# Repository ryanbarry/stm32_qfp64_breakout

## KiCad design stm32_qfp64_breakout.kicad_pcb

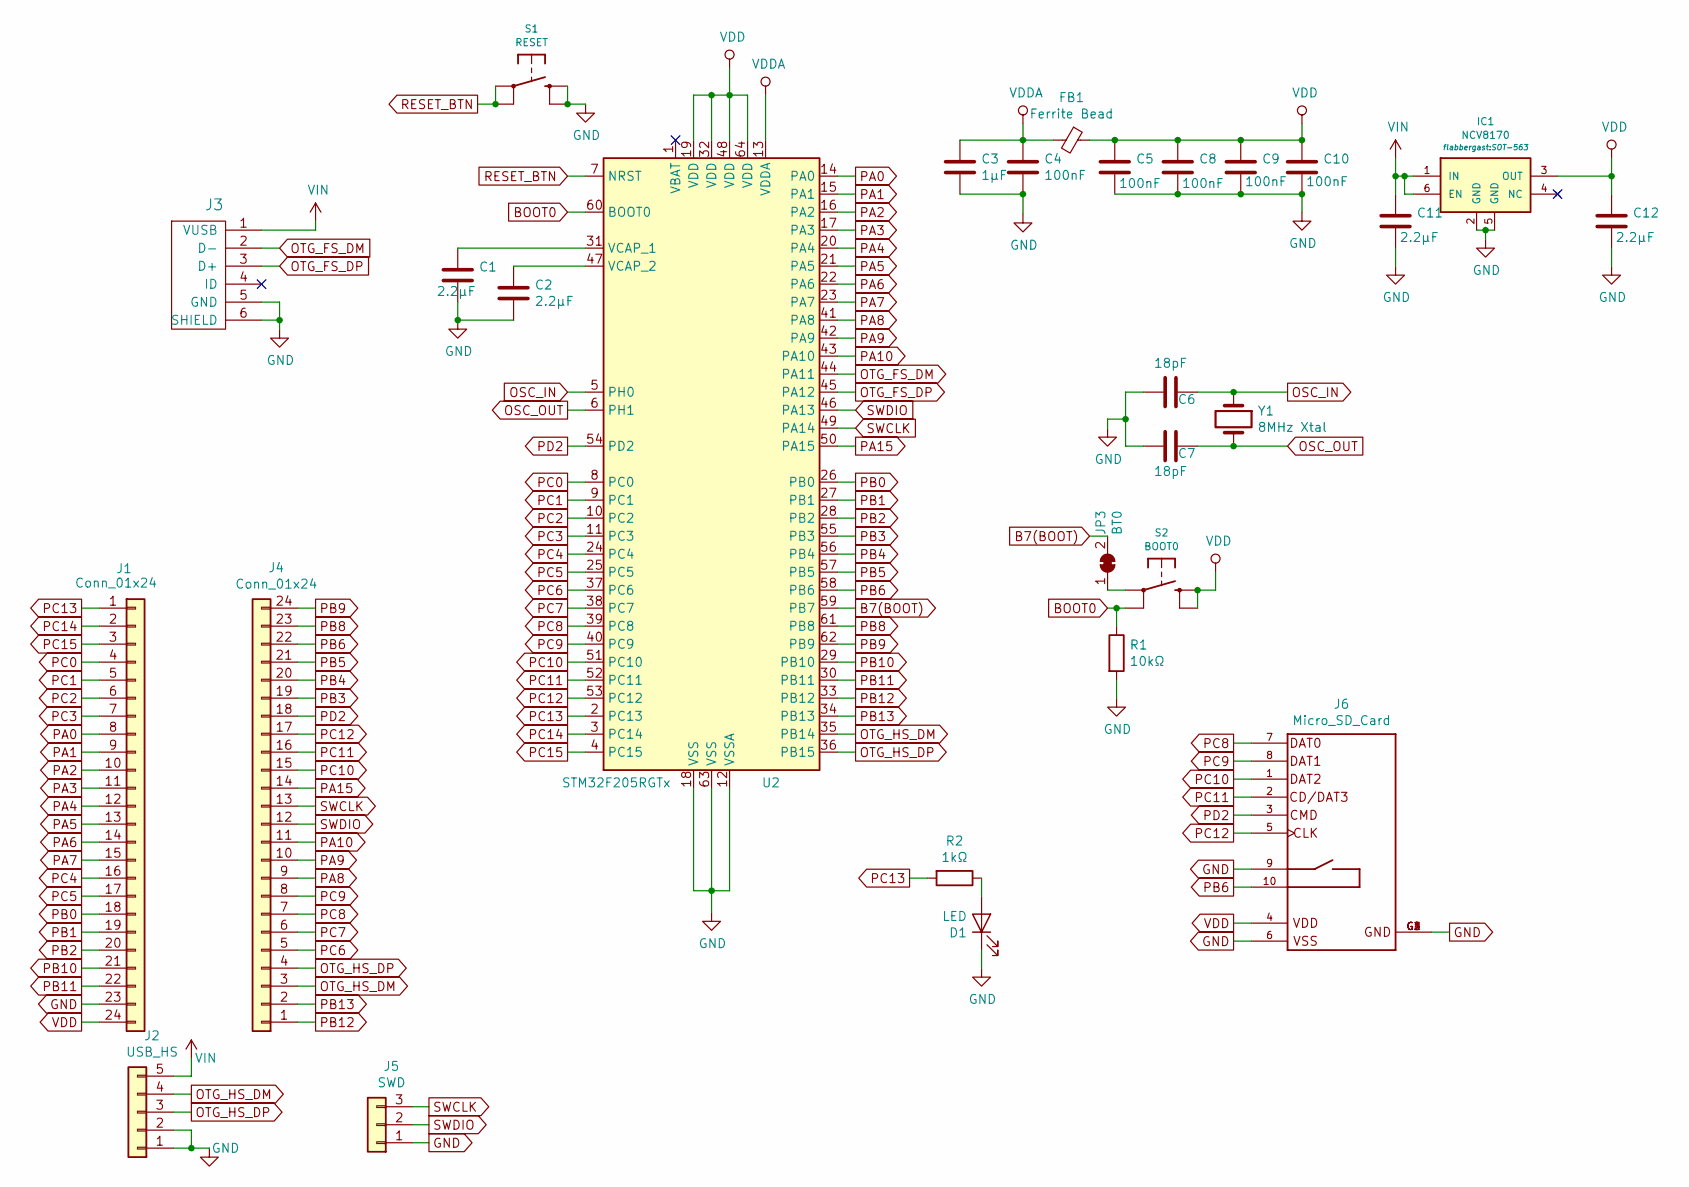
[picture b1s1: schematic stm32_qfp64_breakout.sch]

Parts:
C1, C2, C11, C12: 2.2µF; C_0603_1608Metric
C3: 1µF; C_0603_1608Metric
C4, C5, C8, C9, C10: 100nF; C_0603_1608Metric
C6, C7: 18pF; C_0603_1608Metric
D1: LED; LED-0603
FB1: Ferrite Bead; L_0603_1608Metric
IC1: NCV8170; SOT-563
J1, J4: Conn_01x24; M24_LOCK_NOSILK
J2: USB_HS; PinHeader_1x05_P2.54mm_Vertical
J3: USB_mini_micro_B; USB_microB_2TH_OSHPARK
J5: SWD; PinHeader_1x03_P2.54mm_Vertical
J6: Micro_SD_Card; MOLEX_104031-0811
JP3: BT0; SolderJumper-2_P1.3mm_Open_RoundedPad1.0x1.5mm
R1: 10kΩ; R_0603_1608Metric
R2: 1kΩ; 0603
S1: RESET; TACTILE-SWITCH-SMT-4x3
S2: BOOT0; TACTILE-SWITCH-SMT-4x3
U2: STM32F205RGTx; LQFP-64_10x10mm_P0.5mm
Y1: 8MHz Xtal; CRYSTAL-ABM3

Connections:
B7(BOOT): JP3.2 (B), U2.59 (PB7)
BOOT0: R1.1, S2.2, U2.60 (BOOT0)
GND: C1.1, C2.2, C3.2, C4.2, C5.2, C6.2, C7.2, C8.2, C9.2, C10.2, C11.2, C12.2, D1.1 (K), IC1.2 (GND), IC1.5 (GND), J1.23, J2.1, J2.2, J3.5 (GND), J3.6 (SHIELD), J5.1, J6.6 (VSS), J6.9 (CARD_DET1), J6.G1 (GND), J6.G2 (GND), J6.G3 (GND), J6.G4 (GND), R1.2, S1.3, S1.4, U2.12 (VSSA), U2.18 (VSS), U2.63 (VSS)
unnamed: C1.2, U2.31 (VCAP_1)
unnamed: C2.1, U2.47 (VCAP_2)
unnamed: D1.2 (A), R2.1
unnamed: JP3.1 (A), S2.1
OSC_IN: C6.1, U2.5 (PH0), Y1.1
OSC_OUT: C7.1, U2.6 (PH1), Y1.2
OTG_FS_DM: J3.2 (D-), U2.44 (PA11)
OTG_FS_DP: J3.3 (D+), U2.45 (PA12)
OTG_HS_DM: J2.4, J4.3, U2.35 (PB14)
OTG_HS_DP: J2.3, J4.4, U2.36 (PB15)
PA0: J1.8, U2.14 (PA0)
PA1: J1.9, U2.15 (PA1)
PA2: J1.10, U2.16 (PA2)
PA3: J1.11, U2.17 (PA3)
PA4: J1.12, U2.20 (PA4)
PA5: J1.13, U2.21 (PA5)
PA6: J1.14, U2.22 (PA6)
PA7: J1.15, U2.23 (PA7)
PA8: J4.9, U2.41 (PA8)
PA9: J4.10, U2.42 (PA9)
PA10: J4.11, U2.43 (PA10)
PA15: J4.14, U2.50 (PA15)
PB0: J1.18, U2.26 (PB0)
PB1: J1.19, U2.27 (PB1)
PB2: J1.20, U2.28 (PB2)
PB3: J4.19, U2.55 (PB3)
PB4: J4.20, U2.56 (PB4)
PB5: J4.21, U2.57 (PB5)
PB6: J4.22, J6.10 (CARD_DET2), U2.58 (PB6)
PB8: J4.23, U2.61 (PB8)
PB9: J4.24, U2.62 (PB9)
PB10: J1.21, U2.29 (PB10)
PB11: J1.22, U2.30 (PB11)
PB12: J4.1, U2.33 (PB12)
PB13: J4.2, U2.34 (PB13)
PC0: J1.4, U2.8 (PC0)
PC1: J1.5, U2.9 (PC1)
PC2: J1.6, U2.10 (PC2)
PC3: J1.7, U2.11 (PC3)
PC4: J1.16, U2.24 (PC4)
PC5: J1.17, U2.25 (PC5)
PC6: J4.5, U2.37 (PC6)
PC7: J4.6, U2.38 (PC7)
PC8: J4.7, J6.7 (DAT0), U2.39 (PC8)
PC9: J4.8, J6.8 (DAT1), U2.40 (PC9)
PC10: J4.15, J6.1 (DAT2), U2.51 (PC10)
PC11: J4.16, J6.2 (CD/DAT3), U2.52 (PC11)
PC12: J4.17, J6.5 (CLK), U2.53 (PC12)
PC13: J1.1, R2.2, U2.2 (PC13)
PC14: J1.2, U2.3 (PC14)
PC15: J1.3, U2.4 (PC15)
PD2: J4.18, J6.3 (CMD), U2.54 (PD2)
RESET_BTN: S1.1, S1.2, U2.7 (NRST)
SWCLK: J4.13, J5.3, U2.49 (PA14)
SWDIO: J4.12, J5.2, U2.46 (PA13)
VDD: C5.1, C8.1, C9.1, C10.1, C12.1, FB1.1, IC1.3 (OUT), J1.24, J6.4 (VDD), S2.3, S2.4, U2.19 (VDD), U2.32 (VDD), U2.48 (VDD), U2.64 (VDD)
VDDA: C3.1, C4.1, FB1.2, U2.13 (VDDA)
VIN: C11.1, IC1.1 (IN), IC1.6 (EN), J2.5, J3.1 (VUSB)

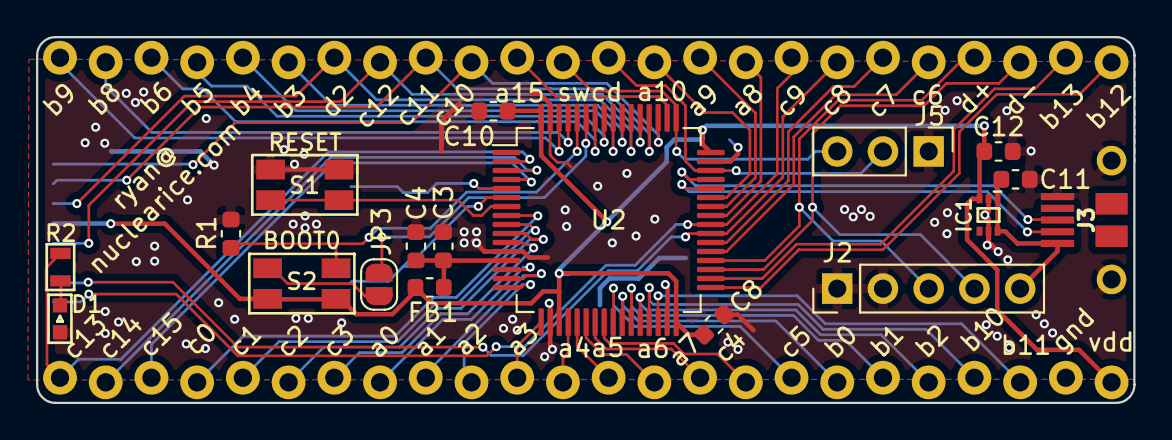
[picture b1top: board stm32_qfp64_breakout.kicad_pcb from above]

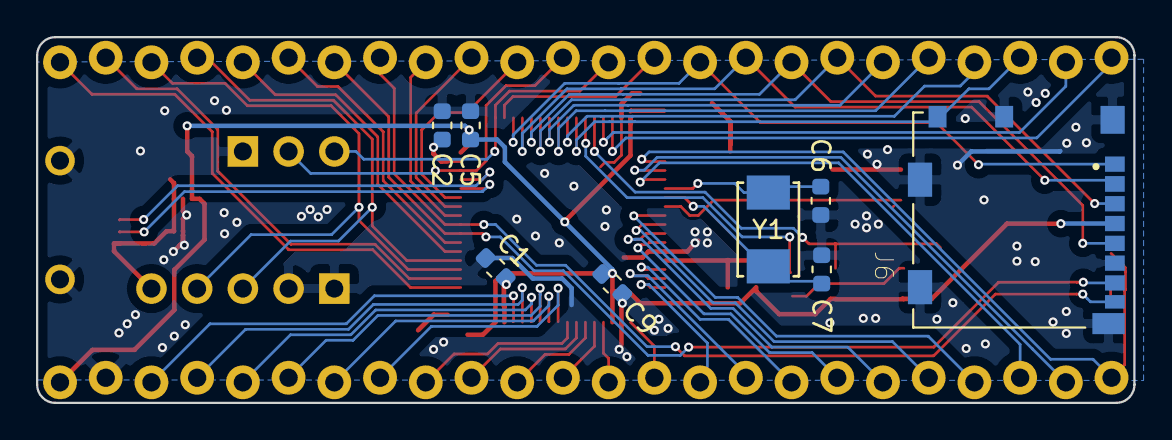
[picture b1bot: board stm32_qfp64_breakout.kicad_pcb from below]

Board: 2 copper layers, 61.0 x 20.3 mm, 28 parts (8 on the bottom side), 61 nets.

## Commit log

2020-01-20 for milling at home
2020-01-22 pins are now 0.7 in apart
2020-01-22 add microsd slot, refine layout
2020-02-10 add README with a pic!
2020-02-10 remove outdated plots
